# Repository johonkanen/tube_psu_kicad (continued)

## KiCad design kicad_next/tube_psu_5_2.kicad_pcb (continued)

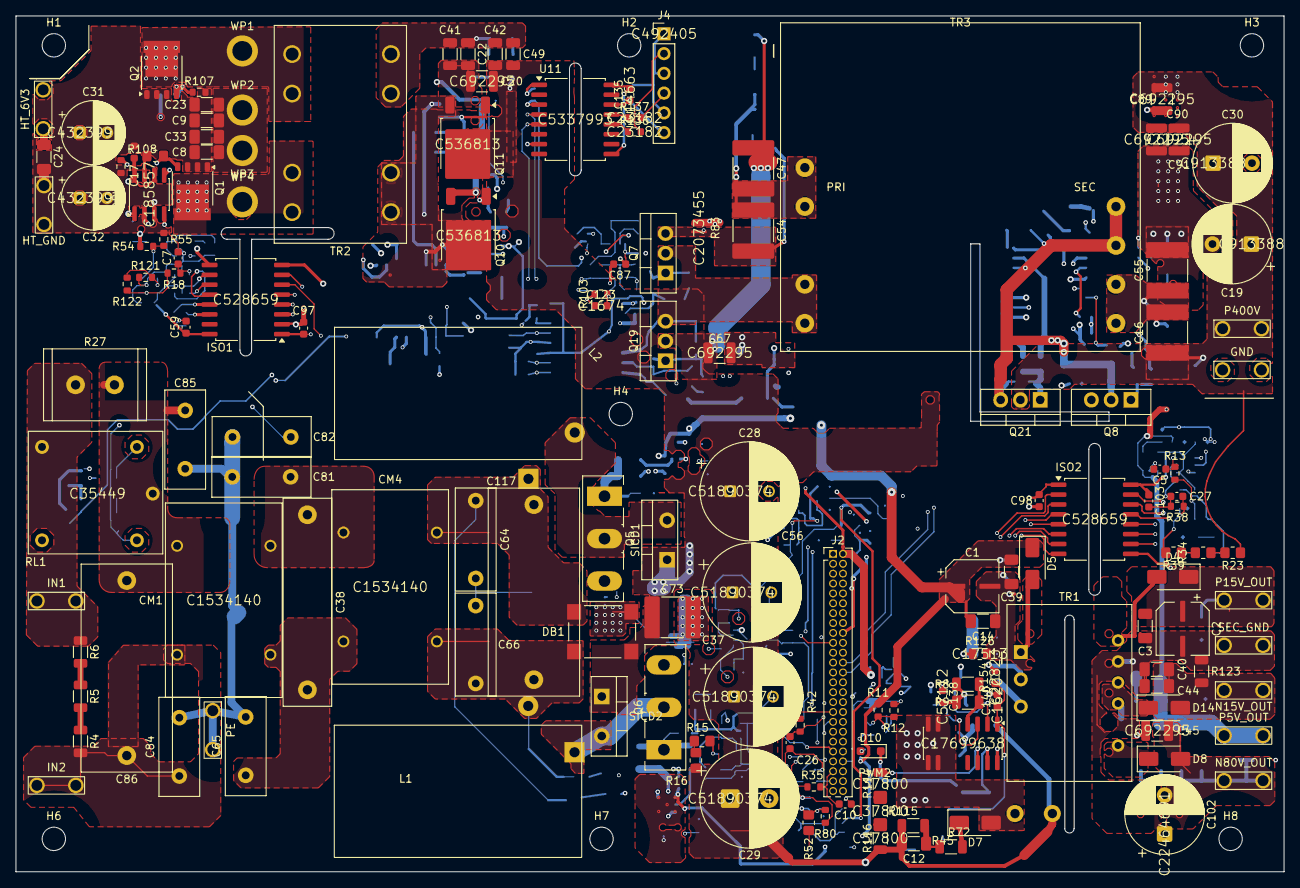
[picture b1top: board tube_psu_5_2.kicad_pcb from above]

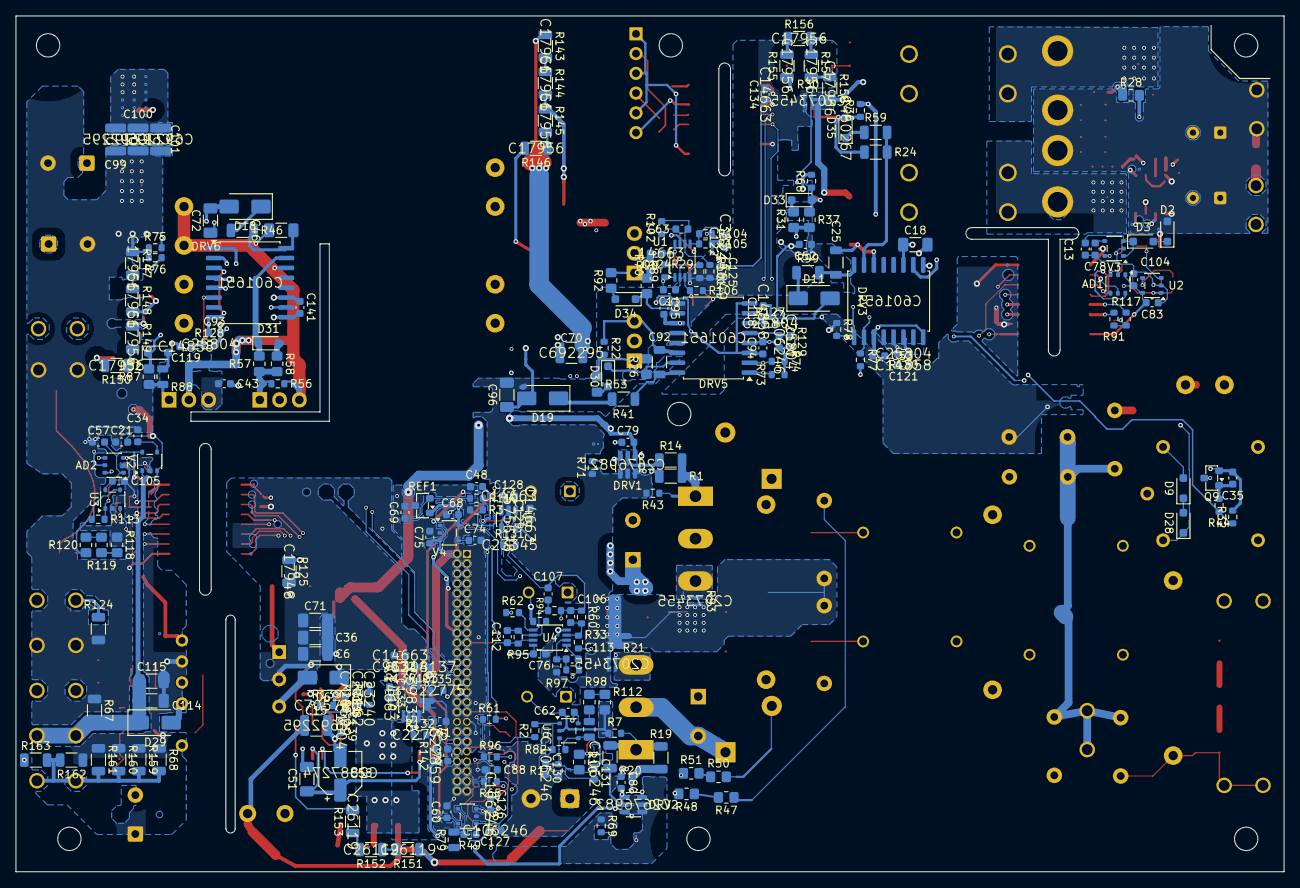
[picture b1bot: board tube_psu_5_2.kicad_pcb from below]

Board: 6 copper layers, 163.0 x 110.0 mm, 380 parts (222 on the bottom side), 202 nets.

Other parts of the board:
H1, H2, H3, H4, H6, H7, H8: MountingHole_3.0mm_NPTH
WP1, WP2, WP3, WP4: WirePad_2.55mm; WirePad_D4.0mm_Drill2.55mm

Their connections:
6V3: WP2.1, WP3.1; also elsewhere on the board
/06 Heaters/Q13_DRAIN: WP1.1; also elsewhere on the board
/06 Heaters/Q14_DRAIN: WP4.1; also elsewhere on the board

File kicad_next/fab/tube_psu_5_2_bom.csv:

Comment,Designator,Footprint,LCSC Part #
ADC121S101,"AD1,AD2",SOT-23-6_Proteus,C74860
220u,"C1,C2",CP_Elec_6.3x7.7_EEEFTE221XAP,C190724
4.7u,"C3,C14,C39,C44,C51,C72",C_1206_3216Metric_Pad1.33x1.80mm_HandSolder,C29823
1n,"C5,C7,C120,C126,C127,C130,C131",C_0603_1608Metric,C106246
22u / CL31A226KAHNNNE,"C6,C36,C40,C114,C115",C_1206_3216Metric_Pad1.33x1.80mm_HandSolder,C12891
10u,"C8,C9,C18,C23,C24,C33",C_1206_3216Metric_Pad1.33x1.80mm_HandSolder,C13585
0603CG5R6C500NT / 5.6p,"C11,C123",C_0603_1608Metric,C1674
470p,C12,C_1206_3216Metric_Pad1.33x1.80mm_HandSolder,C107177
1u / CL10A105KB8NNNC,"C13,C21,C43,C68,C69,C75,C76,C87,C125",C_0603_1608Metric,C15849
FM32X104K631EGG,"C15,C20,C45,C67,C70,C89,C90,C91,C99,C100,C101",C_1210_3225Metric,C692295
1u,"C16,C47,C54,C55",C_2220_5750Metric_Pad1.97x5.40mm_HandSolder,C784102
4.7u / CGA0603X5R475K250JT,"C17,C52,C79,C80,C95",C_0603_1608Metric,C6119856
KCXE5002W680MF,"C19,C30",CP_Radial_D10.0mm_P5.00mm_H50mm,C913388
C1206N332J631T,"C22,C41,C42,C49",C_1206_3216Metric,C105987
1u,"C25,C46,C92,C96",C_1206_3216Metric_Proteus3.15 / C_1206_3216Metric_Pad1.33x1.80mm_HandSolder,C1848
1n2,C27,C_0603_1608Metric,C576816
82u 450V,"C28,C29,C37,C56",CP_Radial_D12.5mm_P5.00mm_Proteus_H45mm / CP_Radial_D12.5mm_P5.00mm_H45mm,C51890374
1500u,"C31,C32",CP_Radial_D8.0mm_P3.50mm_H20mm,C432399
470pF / 470pf,"C34,C78",C_0603_1608Metric,C106211
100n / CC0603KRX7R9BB104,"C35,C48,C53,C59,C61,C74,C93,C94,C97,C98,C103,C104,C105,C124,C128,C129,C132,C133,C134,C135,C141",C_0603_1608Metric,C14663
470nF,C38,C_Rect_L26.5mm_W6.0mm_P22.50mm_MKS4,C3297747
2u2 / 2.2u,"C57,C60,C62,C83",C_0603_1608Metric,C23630
RVT22UF35V67RV0104,C58,CP_Elec_5x5.4,C2887274
CL10C120JB8NNNC / 12p,"C63,C122",C_0603_1608Metric,C38523
47n,"C64,C66",C_Rect_L13.0mm_W5.0mm_P10.00mm_FKS3_FKP3_MKS4,C3298405
2n2,"C65,C81,C82,C84,C85",C_Disc_D12.5mm_W5.0mm_P7.50mm,C96522
100u,C71,C_1206_3216Metric_Pad1.33x1.80mm_HandSolder,C6119961
2.2u,C73,C_2220_5750Metric_Pad1.97x5.40mm_HandSolder,C445674
100p,"C77,C88,C118,C119,C121",C_0603_1608Metric,C14858
680n,"C86,C117",C_Rect_L26.5mm_W11.5mm_P22.50mm_MKS4,C2888216
56u 250V,C102,CP_Radial_D10.0mm_P5.00mm_H18mm,C22464691
20p,"C106,C107,C112,C113",C_0603_1608Metric,C1648
10n,C138,C_0603_1608Metric,C57112
2.2n,C139,C_0603_1608Metric,C1604
470p,C140,C_0603_1608Metric,C1620
SCF20-05-550,"CM1,CM4",L_CommonMode_SCF20-05-550,C1534140
ZLLS400TA,"D2,D3,D9,D10,D28,D30,D31,D32,D33,D34,D35",D_SOD-323_AC,C460267
ES1D,"D4,D5,D6,D14,D29",D_SMA_AC,C116492
S1M,"D7,D11,D18,D19",D_SMA_AC,C64915
US1M,D8,D_SMA_AC,C412437
UCC27511ADBVR,"DRV1,DRV2",SOT-23-6,C2676982
UCC21520DWR,"DRV3,DRV5,DRV6",SOIC-16W_7.5x10.3mm_P1.27mm,C601651
UCC27524ADR,DRV4,SOIC-8_3.9x4.9mm_P1.27mm,C185857
CA-IS3761LW,"ISO1,ISO2",SOIC-16W_7.5x10.3mm_P1.27mm_Slot8.0_T_ISO1 / SOIC-16W_7.5x10.3mm_P1.27mm_Slot11.1,C528659
X1321FV-2x25-C43D24,J2,PinSocket_2x25_P1.27mm_Vertical_XKB_X1321FV,C2881768
PZ254V-11-06P,J4,PinHeader_1x06_P2.54mm_Vertical,C492405
ICE5AR0680AGXUMA1,PWM2,PG-DSO-12_3.9x9.9mm_P1.27mm,C17699638
BUK9Y15-60E,"Q1,Q2",LFPAK56_Proteus,C458196
BSS138LT1G,Q9,SOT-23_Proteus,C82045
IPD60R280P7S,"Q10,Q11",TO-252-2,C536813
5R,"R1,R14,R19,R20",R_1206_3216Metric,C2999547
0603WAF1000T5E / 100R / 100,"R2,R18,R61,R65,R96,R132,R135",R_0603_1608Metric,C22775
0603WAF1961T5E,R3,R_0603_1608Metric,C22854
1206W4F1803T5E,"R4,R5,R6",R_1206_3216Metric,C17923
10k,"R7,R22,R36,R43,R56,R66,R69,R70,R71,R73,R74,R75,R76,R77,R78,R127,R128,R129,R130",R_0603_1608Metric,C25804
FRC1206F1R37TS,"R8,R9",R_1206_3216Metric,C3000600
1M,"R10,R15,R16,R23,R34,R39,R47,R48,R50,R51,R52,R79,R109,R111,R112,R118,R119,R120",R_0805_2012Metric_Pad1.20x1.40mm_HandSolder / R_0805_2012Metric_Proteus,C17514
22k,R11,R_0603_1608Metric,C31850
4.7k,"R12,R140",R_0603_1608Metric,C23162
1k / 0603WAF1001T5E,"R13,R107,R108,R110",R_0603_1608Metric,C21190
15k,"R17,R38,R54,R82,R102,R105,R113,R121",R_0603_1608Metric,C22809
KRL2012E-M-R005-F-T5,"R21,R30,R83,R93",R_0508_1220Metric_KRL2012,C2073455
10R,R24,R_1206_3216Metric,C17903
40R,"R26,R57,R87,R90",R_0805_2012Metric_Pad1.20x1.40mm_HandSolder,C2933439
4.7R,"R28,R63",R_0805_2012Metric_Proteus2.13,C17675
330R,"R29,R33,R62,R94,R97,R101,R104,R106",R_0603_1608Metric,C23138
3.3R,"R31,R53,R58,R88,R92",R_0805_2012Metric_Pad1.20x1.40mm_HandSolder / R_0805_2012Metric_Proteus,C22356719
2.2k,"R32,R44",R_0603_1608Metric,C4190
33R / 33,"R35,R42",R_0603_1608Metric,C23140
10R,R37,R_0805_2012Metric_Pad1.20x1.40mm_HandSolder,C17415
2R,"R41,R46,R99",R_1206_3216Metric,C2907381
1M,R45,R_1206_3216Metric,C17927
0603WAF1202T5E,"R49,R80",R_0603_1608Metric,C22790
6.8k,"R55,R60,R95,R98,R100,R122",R_0603_1608Metric,C23212
3.3R,R59,R_1206_3216Metric,C2930397
12.1K,R67,R_1206_3216Metric,C247391
WR12X7322FTL / 73.2k,"R68,R159,R160,R161,R162,R163",R_1206_3216Metric,C368302
100R,R72,R_1206_3216Metric,C17901
33k,"R89,R103",R_0603_1608Metric,C4216
8.2k,"R91,R117",R_0603_1608Metric,C25981
1206W4F4704T5E,"R114,R115,R116",R_1206_3216Metric,C37800
1206W4F4701T5E,R123,R_1206_3216Metric,C17936
CR1206F2K61P05Z,R124,R_1206_3216Metric,C245506
2.2k,R125,R_1206_3216Metric,C17948
1k,R126,R_0805_2012Metric,C17513
22R,R131,R_0603_1608Metric,C23345
15k 0.1%,R133,R_0603_1608Metric,C318137
10k 0.1%,R134,R_0603_1608Metric,C95204
47R,"R136,R137",R_0603_1608Metric,C23182
88.7k 0.1%,R138,R_0603_1608Metric,C728599
49.9k 0.1%,R139,R_0603_1608Metric,C705780
750k,R141,R_0603_1608Metric,C23240
10R,R142,R_0603_1608Metric,C22859
220k,"R143,R144,R145,R146,R147,R148,R149,R150,R155,R156,R157,R158",R_1206_3216Metric,C17956
10M,"R151,R152,R153",R_1206_3216Metric,C26119
178k,R154,R_0603_1608Metric,C22823
REF3325AIDBZR,REF1,SOT-23_Proteus,C69039
SONGLE RELAY,RL1,Relay_Songle_SRD_5pin,C35449
LMH6643,"U1,U4",TSSOP-8_3x3mm_P0.65mm,C478382
TLV316IDBVR,"U2,U3,U6,U8,U9",SOT-23-5_Proteus / SOT-23-5,C575578
TLV9062IDGKR,U10,VSSOP-8_3x3mm_P0.65mm,C398356
CA-IS3721HW,U11,SOIC-16W_7.5x10.3mm_P1.27mm_Slot8.0,C5337993
MIC5205,"V2,V3",SOT-23-5_Proteus,C37970
TPS73033,V4,SOT-23-5_Proteus,C57424
